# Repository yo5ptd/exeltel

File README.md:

# exeltel
exeltel cartridge for 27c256 eprom

## Introduction

exeltel exl 100, i had no basic catridge to test it, so i made one. 

## Hardware Documentation
Idea is to make it without vias, so i can use my CNC to mill PCB. I just added a pullup resistor and a cut jumper, so i can use 27c128 or 27c64 eproms too (not tested yet). Just make sure that when inserted, the eprom faces down (bottom of PCB marked with the letter B is facing up.

### Schematic and PCB Layout

[Schematic](sch.pdf)

[PCB Layout](pcb.pdf)

[Image](exeltel.png)

### Bill of Materials

Component Type | Reference | Description                             | Quantity | Possible Sources and Notes
-------------- | --------- | --------------------------------------- | -------- | --------------------------
PCB            |           | exeltel     	                           | 1        | mill it on your CNC
Capacitor      | C1        | 0.1 uF ceramic                          | 1        | regular ceramif filter cap
Resistor       | R1 	     | 10 k pullup                             | 1        | optional for  27c128 or 27c64

I was able to run exelbasic. I used ROM's from https://archive.org/details/Exelvision_EXL_100_TOSEC_2012_04_23

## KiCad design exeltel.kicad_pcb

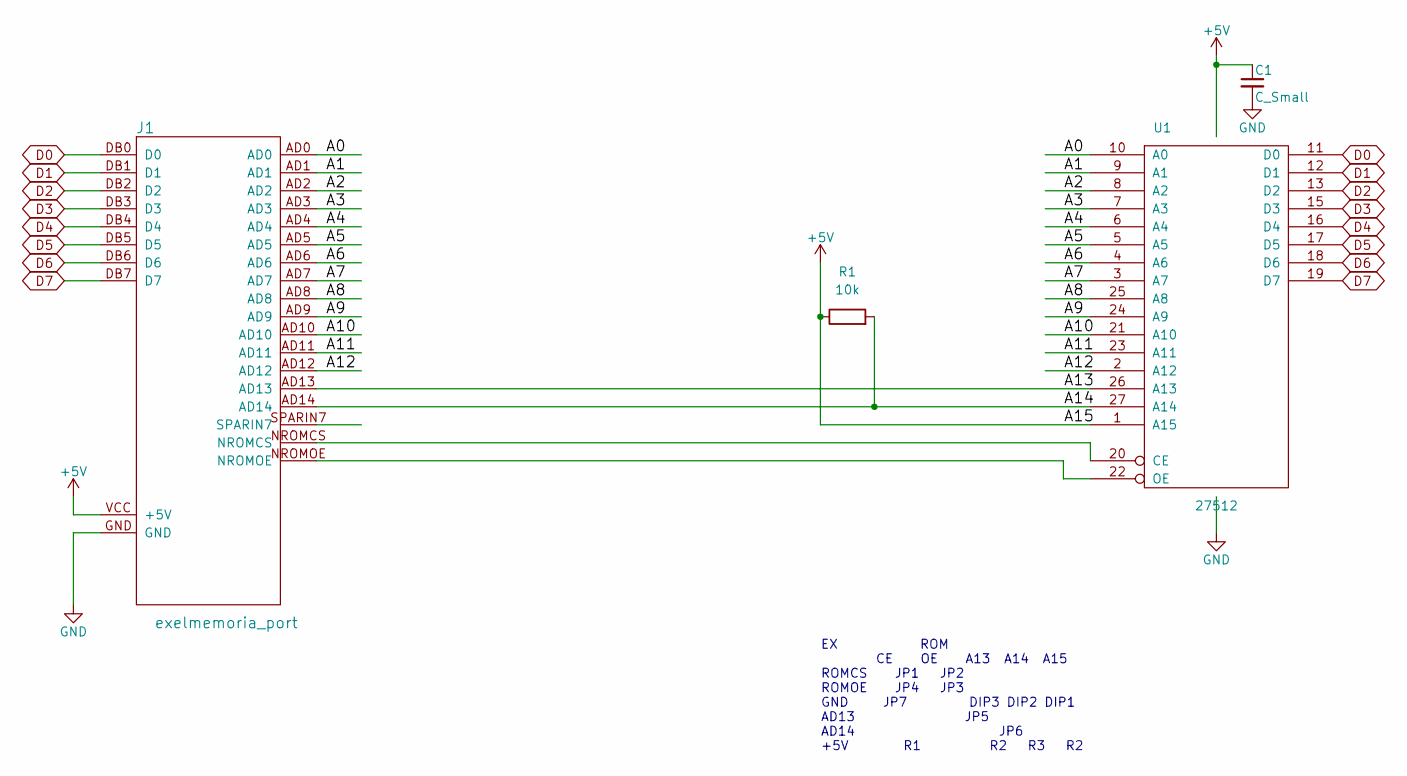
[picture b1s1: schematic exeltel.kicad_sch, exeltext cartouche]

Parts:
C1: C_Small; C_Rect_L10.0mm_W2.5mm_P7.50mm_MKS4
J1: exelmemoria_port; exeltel_edge
R1: 10k; R_Axial_DIN0207_L6.3mm_D2.5mm_P10.16mm_Horizontal
U1: 27512; DIP-28_W15.24mm_Socket_LongPads

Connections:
+5V: C1.1, J1.VCC (+5V), R1.1, U1.1 (A15), U1.28 (VCC)
/A0: J1.AD0, U1.10 (A0)
/A1: J1.AD1, U1.9 (A1)
/A2: J1.AD2, U1.8 (A2)
/A3: J1.AD3, U1.7 (A3)
/A4: J1.AD4, U1.6 (A4)
/A5: J1.AD5, U1.5 (A5)
/A6: J1.AD6, U1.4 (A6)
/A7: J1.AD7, U1.3 (A7)
/A8: J1.AD8, U1.25 (A8)
/A9: J1.AD9, U1.24 (A9)
/A10: J1.AD10, U1.21 (A10)
/A11: J1.AD11, U1.23 (A11)
/A12: J1.AD12, U1.2 (A12)
/A13: J1.AD13, U1.26 (A13)
/A14: J1.AD14, R1.2, U1.27 (A14)
D0: J1.DB0 (D0), U1.11 (D0)
D1: J1.DB1 (D1), U1.12 (D1)
D2: J1.DB2 (D2), U1.13 (D2)
D3: J1.DB3 (D3), U1.15 (D3)
D4: J1.DB4 (D4), U1.16 (D4)
D5: J1.DB5 (D5), U1.17 (D5)
D6: J1.DB6 (D6), U1.18 (D6)
D7: J1.DB7 (D7), U1.19 (D7)
GND: C1.2, J1.GND, U1.14 (GND)
unnamed: J1.NROMCS, U1.20 (CE)
unnamed: J1.NROMOE, U1.22 (OE)

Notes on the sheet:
EX ROM CE OE A13 A14 A15 ROMCS JP1 JP2 ROMOE JP4 JP3 GND JP7 DIP3 DIP2 DIP1 AD13 JP5 AD14 JP6 +5V R1 R2 R3 R2

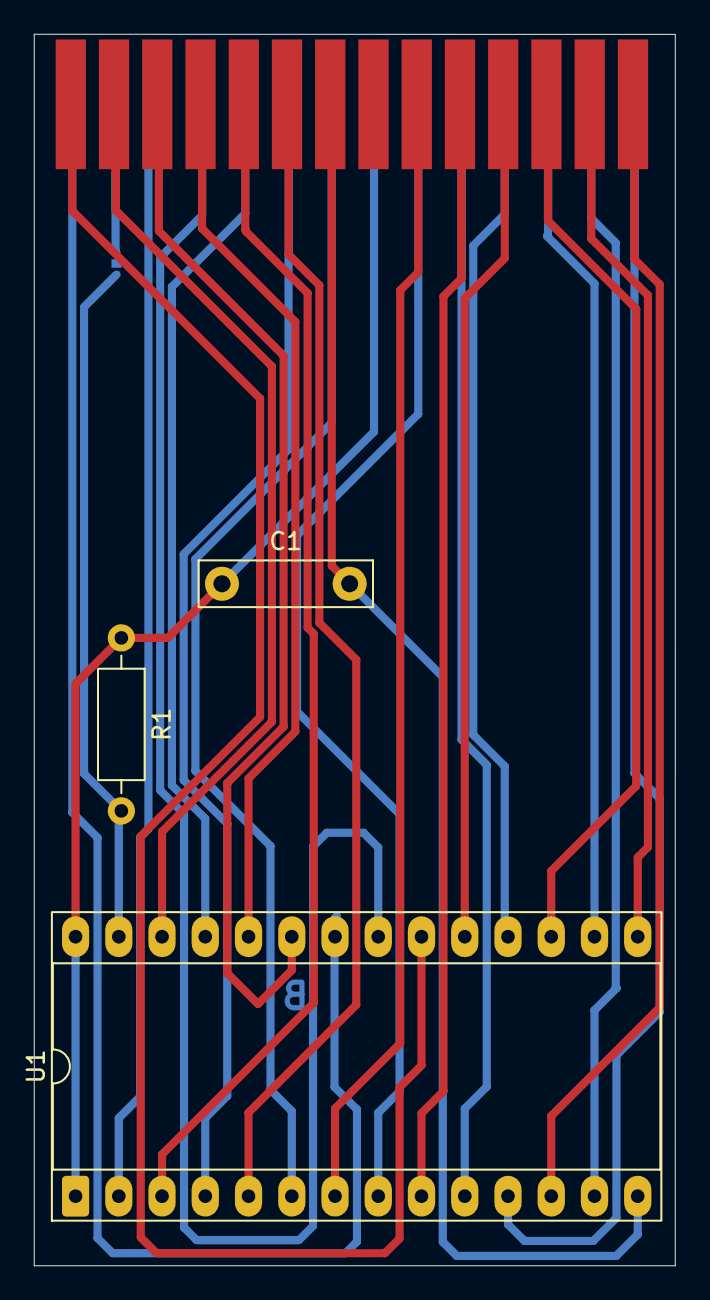
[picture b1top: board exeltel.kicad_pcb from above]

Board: 2 copper layers, 37.7 x 72.3 mm, 4 parts (0 on the bottom side), 27 nets.
